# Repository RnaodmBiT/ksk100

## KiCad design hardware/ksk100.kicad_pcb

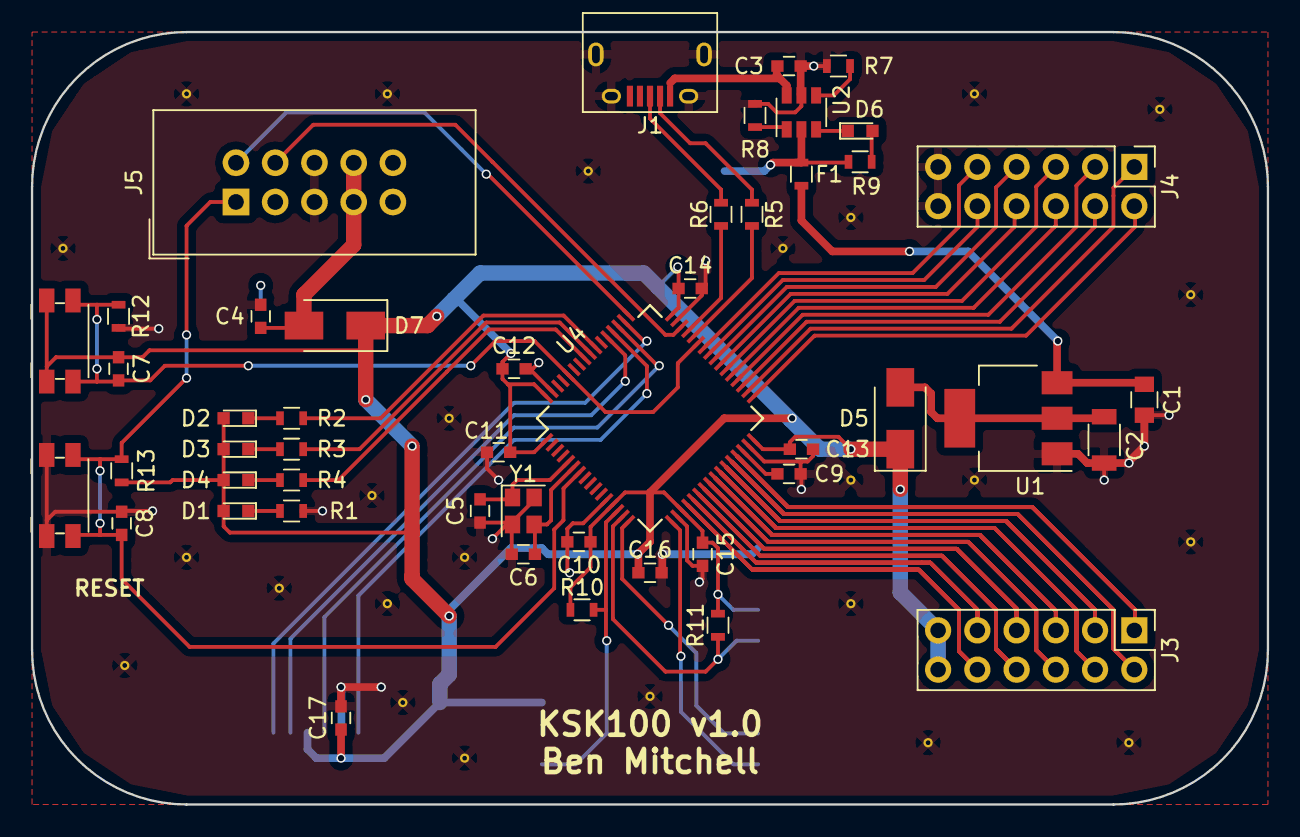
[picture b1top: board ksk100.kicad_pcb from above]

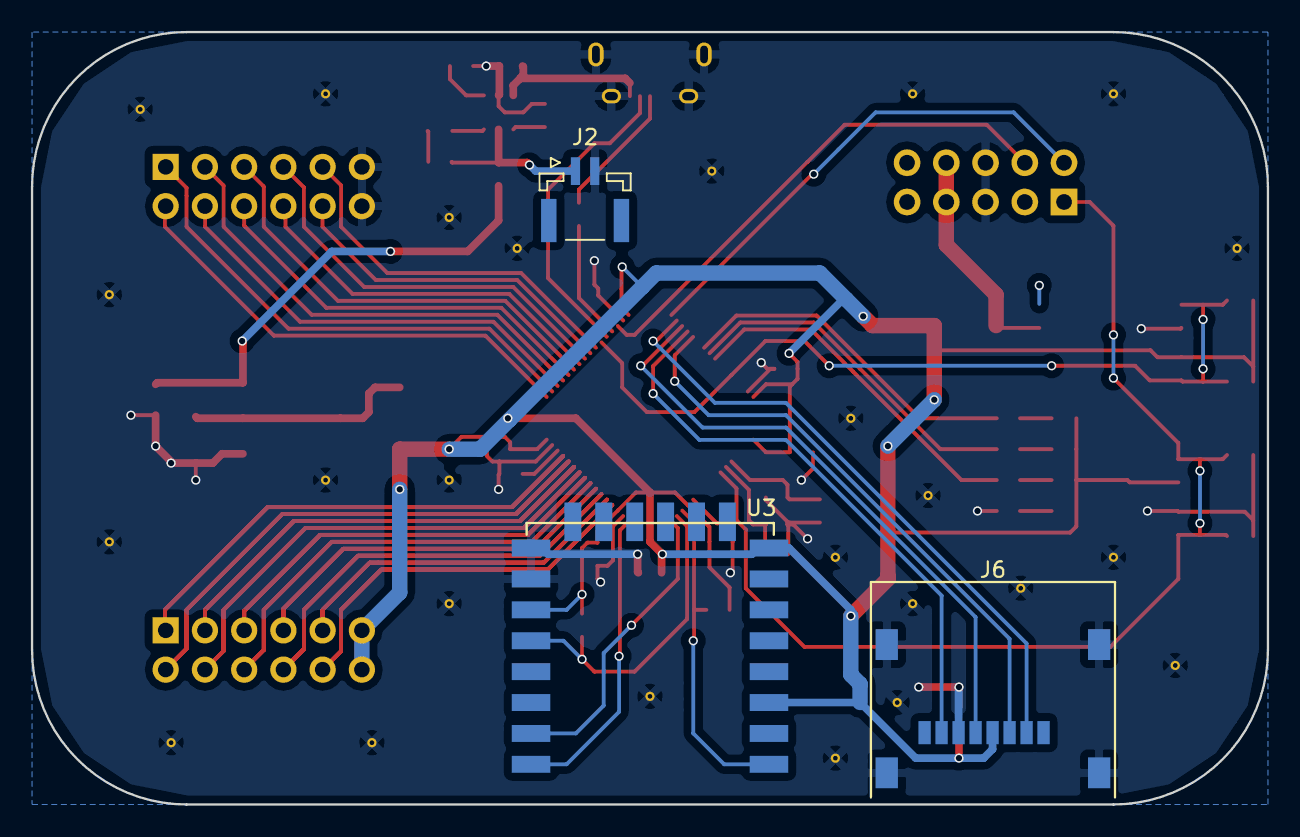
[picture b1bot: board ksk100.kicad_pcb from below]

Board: 2 copper layers, 80.0 x 50.0 mm, 51 parts (3 on the bottom side), 57 nets.

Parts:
C1: 10uF; C_0805
C2: 22uF; C_1206
C3, C10: 1uF; C_0603
C4: 10uF; C_0603
C5, C6: 10pF; C_0603
C7, C8, C11, C12, C13, C14, C15, C16, C17: 100nF; C_0603
C9: 4.7uF; C_0603
D1: POWER; LED_0603
D2, D6: RED; LED_0603
D3: GREEN; LED_0603
D4: BLUE; LED_0603
D5, D7: 1A; D_SMA
F1: 500mA; R_0603
J1: USB_OTG; USB_Micro-B
J2: Conn_01x02; JST_GH_SM02B-GHS-TB_02x1.25mm_Angled
J3, J4: Conn_02x06_Odd_Even; Pin_Header_Straight_2x06_Pitch2.54mm
J5: Conn_02x05_Odd_Even; IDC-Header_2x05_Pitch2.54mm_Straight
J6: Micro_SD_Card; MicroSd_Wurth_693072010801
R1, R3: 800; R_0603
R2: 1k5; R_0603
R4: 400; R_0603
R5, R6: 27; R_0603
R7: 1k; R_0603
R8, R10, R11, R12, R13: 10k; R_0603
R9: 3k3; R_0603
SW1: BOOT; Panasonic_EVQPUJ_EVQPUA
SW2: RESET; Panasonic_EVQPUJ_EVQPUA
U1: LT1117-3.3; SOT-223-3_TabPin2
U2: BQ21040; SOT-23-6
U3: ESP-12F; ESP-12E_SMD
U4: STM32F411RETx; LQFP-64_10x10mm_Pitch0.5mm
Y1: 12MHz; Crystal_SMD_2520-4pin_2.5x2.0mm

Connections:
+3V3: C7.1, C10.1, C11.1, C12.1, C13.1, C14.1, C15.1, C16.1, C17.1, D1.2, D2.2, D3.2, D4.2, D5.1, D7.1, J3.11, J3.12, J6.4, R10.1, R11.2, R13.1, SW1.1, U3.3, U3.8, U3.11, U4.1, U4.13, U4.19, U4.32, U4.48, U4.64
+BATT: F1.1, J2.1, R9.1, U2.2
/BLUE: R4.1, U4.57
/BOOT: C7.2, R12.1, SW1.2, U4.43, U4.60
/ESP_nPROG: R11.1, U3.12, U4.15
/ESP_nRST: R10.2, U3.1, U4.14
/GREEN: R3.1, U4.56
/PA2: U3.15, U4.16
/PA3: U3.16, U4.17
/PA4: J3.10, U4.20
/PA5: J3.9, U4.21
/PA6: J3.8, U4.22
/PA7: J3.7, U4.23
/PA8: J4.10, U4.41
/PA9: J4.9, U4.42
/PA11: R5.2, U4.44
/PA12: R6.2, U4.45
/PA13: J5.4, U4.46
/PA14: J5.2, U4.49
/PA15: J6.2, U4.50
/PB0: J3.4, U4.26
/PB1: J3.3, U4.27
/PB2: J3.2, U4.28
/PB3: R2.1, U4.55
/PB10: J3.1, U4.29
/PB12: J4.2, U4.33
/PB13: J4.1, U4.34
/PB14: J4.4, U4.35
/PB15: J4.3, U4.36
/PC4: J3.6, U4.24
/PC5: J3.5, U4.25
/PC6: J4.6, U4.37
/PC7: J4.5, U4.38
/PC8: J4.8, U4.39
/PC9: J4.7, U4.40
/PC10: J6.5, U4.51
/PC11: J6.7, U4.52
/PC12: J6.3, U4.53
/nRESET: C8.2, J5.1, R13.2, SW2.2, U4.7
GND: C1.2, C2.2, C3.2, C4.2, C5.2, C6.2, C8.1, C9.2, C10.2, C11.2, C12.2, C13.2, C14.2, C15.2, C16.2, C17.2, J1.5, J1.6, J2.2, J4.11, J4.12, J5.5, J5.6, J6.6, J6.9, R1.1, R7.2, R8.1, R12.2, SW2.1, U1.1, U2.5, U3.9, U3.10, U4.12, U4.18, U4.31, U4.47, U4.63, Y1.2, Y1.4
unnamed: C1.1, F1.2, U1.3
unnamed: C2.1, D5.2, U1.2
unnamed: C3.1, J1.1, U2.6
unnamed: C4.1, D7.2, J5.7, J5.8
unnamed: C5.1, U4.5, Y1.1
unnamed: C6.1, U4.6, Y1.3
unnamed: C9.1, U4.30
unnamed: D1.1, R1.2
unnamed: D2.1, R2.2
unnamed: D3.1, R3.2
unnamed: D4.1, R4.2
unnamed: D6.1, U2.3
unnamed: D6.2, R9.2
unnamed: J1.2, R5.1
unnamed: J1.3, R6.1
unnamed: R7.1, U2.4
unnamed: R8.2, U2.1

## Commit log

2018-01-09 Initial commit with fundamental STM32F411 schematic setup
2018-01-10 Finished the schematic. Might need a bit more tweaking. Started laying out the PCB
2018-01-15 Finish work on the v1.0 PCB
2018-01-16 Plot the gerbers and start working on the motor driver
